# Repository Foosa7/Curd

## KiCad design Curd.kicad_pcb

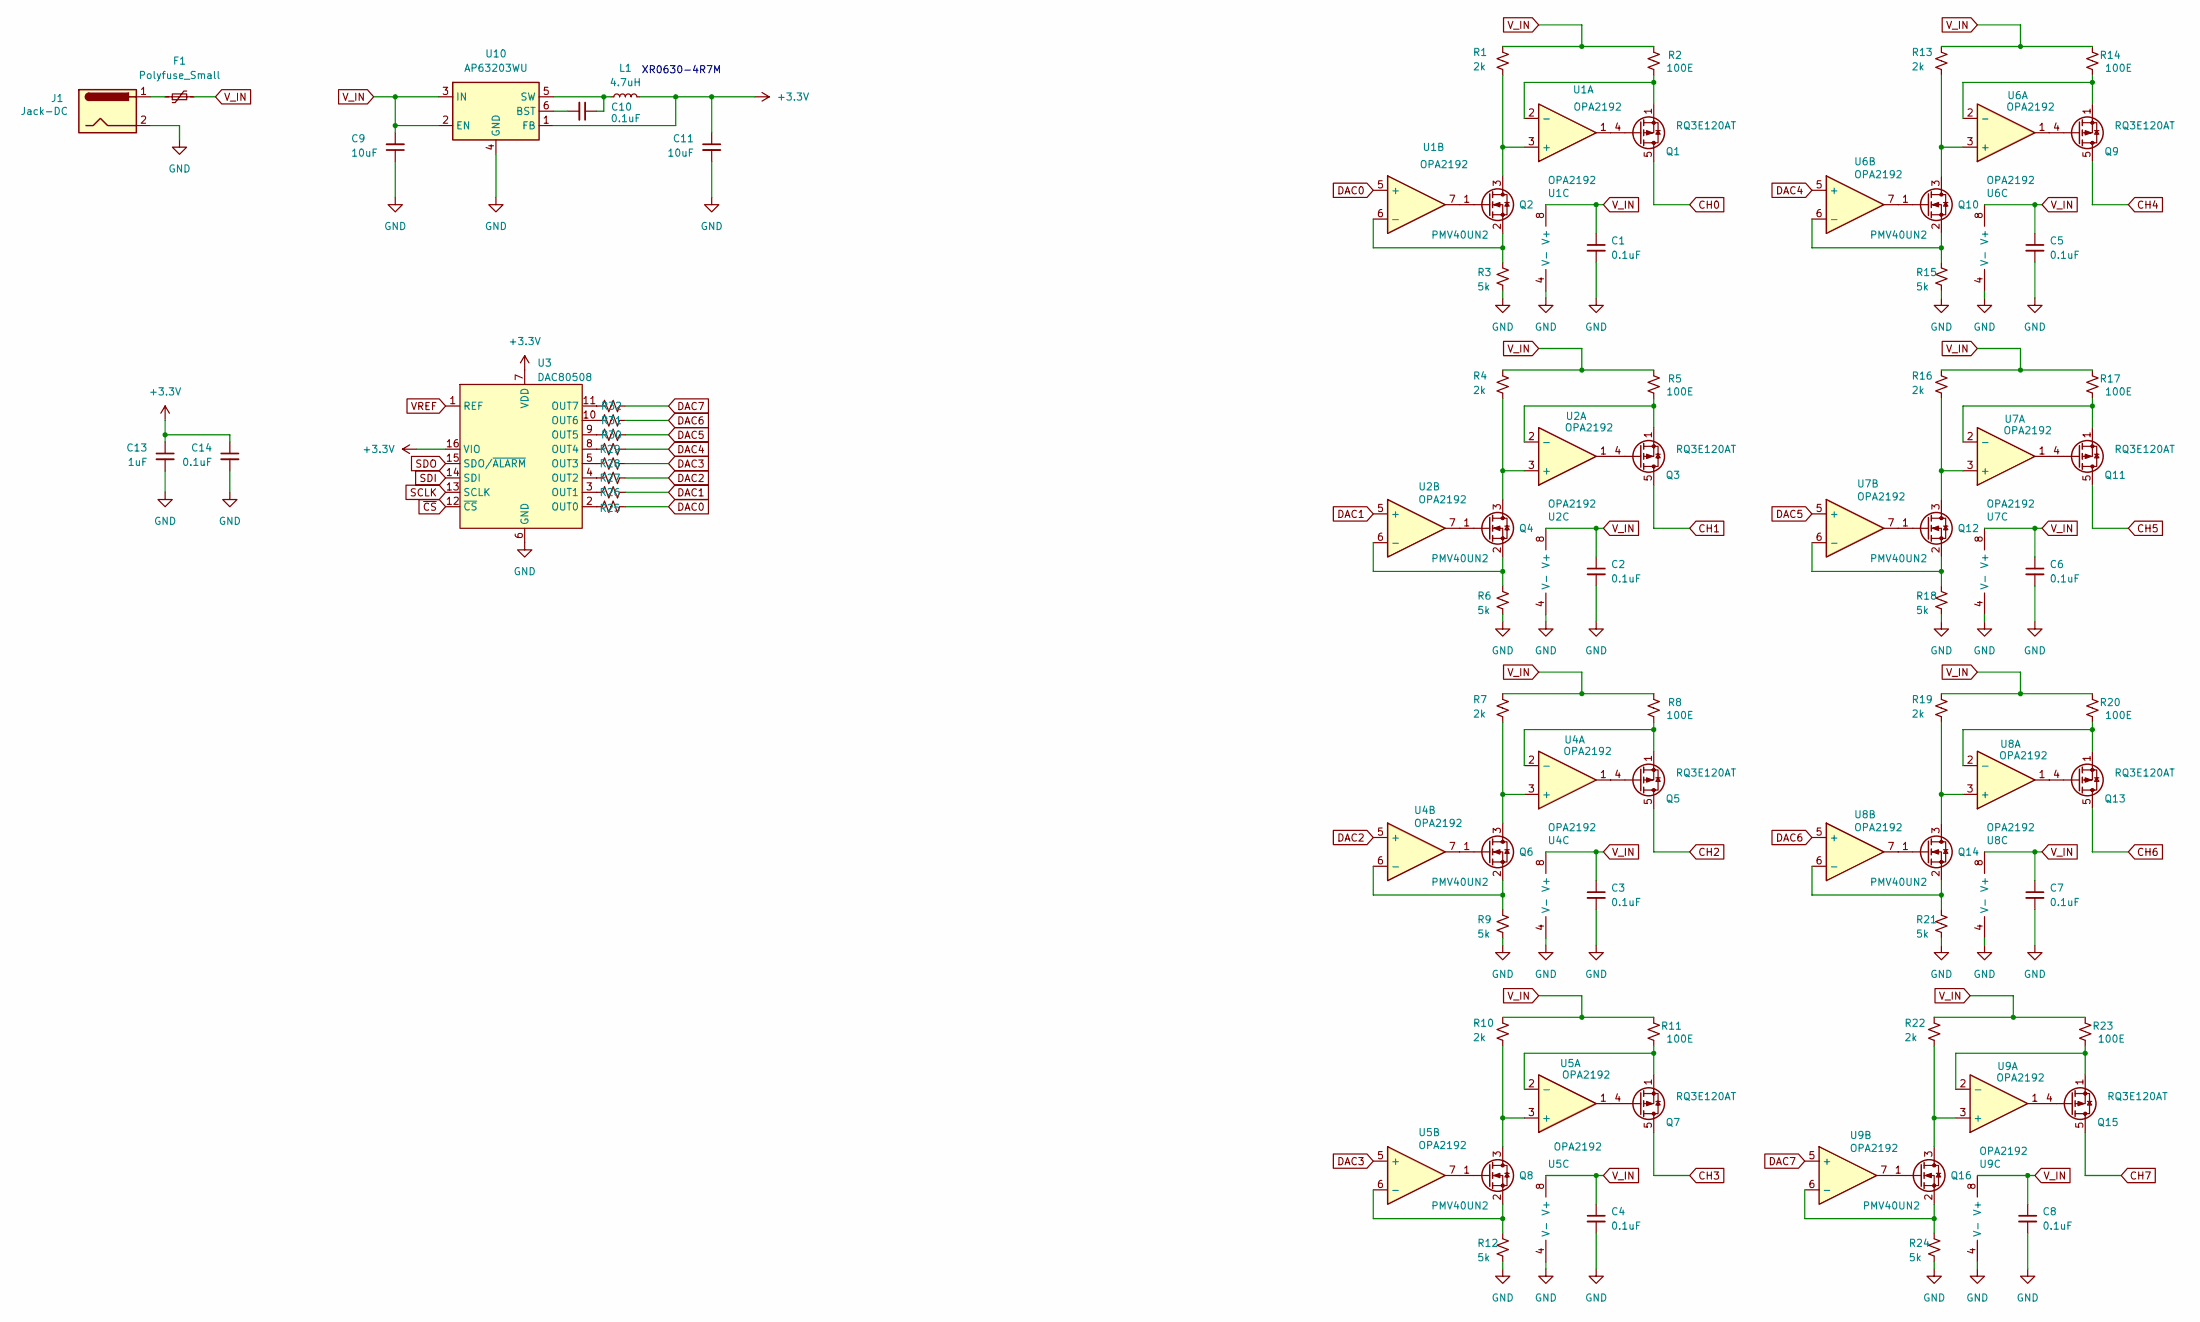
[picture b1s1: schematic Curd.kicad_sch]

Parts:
C1, C2, C3, C4, C5, C6, C7, C8, C10, C14: 0.1uF; C_0603_1608Metric
C9, C11: 10uF; C_0603_1608Metric
C13: 1uF; C_0603_1608Metric
F1: Polyfuse_Small
J1: Jack-DC
L1: 4.7uH; XR0630-4R7M
Q1, Q3, Q5, Q7, Q9, Q11, Q13, Q15: RQ3E120AT; HSMT8
Q2, Q4, Q6, Q8, Q10, Q12, Q14, Q16: PMV40UN2; SOT-23-3
R1, R4, R7, R10, R13, R16, R19, R22: 2k; R_0603_1608Metric
R2, R5, R8, R11, R14, R17, R20, R23: 100E; R_0603_1608Metric
R3, R6, R9, R12, R15, R18, R21, R24: 5k; R_0603_1608Metric
R25, R26, R27, R28, R29, R30, R31, R32: R_0603_1608Metric
U1, U2, U4, U5, U6, U7, U8, U9: OPA2192; SOIC-8_3.9x4.9mm_P1.27mm
U3: DAC80508; WQFN-16-1EP_3x3mm_P0.5mm_EP1.6x1.6mm
U10: AP63203WU; TSOT-23-6

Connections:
+3.3V: C11.1, C13.1, C14.1, L1.2, U3.7 (VDD), U3.16 (VIO), U10.1 (FB)
CH0: Q1.5, Q1.6 (D), Q1.7 (D), Q1.8 (D)
CH1: Q3.5, Q3.6 (D), Q3.7 (D), Q3.8 (D)
CH2: Q5.5, Q5.6 (D), Q5.7 (D), Q5.8 (D)
CH3: Q7.5, Q7.6 (D), Q7.7 (D), Q7.8 (D)
CH4: Q9.5, Q9.6 (D), Q9.7 (D), Q9.8 (D)
CH5: Q11.5, Q11.6 (D), Q11.7 (D), Q11.8 (D)
CH6: Q13.5, Q13.6 (D), Q13.7 (D), Q13.8 (D)
CH7: Q15.5, Q15.6 (D), Q15.7 (D), Q15.8 (D)
DAC0: R25.2, U1.5 (+)
DAC1: R26.2, U2.5 (+)
DAC2: R27.2, U4.5 (+)
DAC3: R28.2, U5.5 (+)
DAC4: R29.2, U6.5 (+)
DAC5: R30.2, U7.5 (+)
DAC6: R31.2, U8.5 (+)
DAC7: R32.2, U9.5 (+)
GND: C1.2, C2.2, C3.2, C4.2, C5.2, C6.2, C7.2, C8.2, C9.1, C11.2, C13.2, C14.2, J1.2, R3.2, R6.2, R9.2, R12.2, R15.2, R18.2, R21.2, R24.2, U1.4 (V-), U2.4 (V-), U3.6 (GND), U3.17 (THERMAL), U4.4 (V-), U5.4 (V-), U6.4 (V-), U7.4 (V-), U8.4 (V-), U9.4 (V-), U10.4 (GND)
unnamed: F1.1, J1.1
unnamed: Q1.4, U1.1
unnamed: Q2.1, U1.7
unnamed: Q3.4, U2.1
unnamed: Q4.1, U2.7
unnamed: Q5.4, U4.1
unnamed: Q6.1, U4.7
unnamed: Q7.4, U5.1
unnamed: Q8.1, U5.7
unnamed: Q9.4, U6.1
unnamed: Q10.1, U6.7
unnamed: Q11.4, U7.1
unnamed: Q12.1, U7.7
unnamed: Q13.4, U8.1
unnamed: Q14.1, U8.7
unnamed: Q15.4, U9.1
unnamed: Q16.1, U9.7
unnamed: Q2.3, R1.2, U1.3 (+)
unnamed: Q1.1, Q1.2 (S), Q1.3 (S), R2.1, U1.2 (-)
unnamed: Q2.2, R3.1, U1.6 (-)
unnamed: Q4.3, R4.2, U2.3 (+)
unnamed: Q3.1, Q3.2 (S), Q3.3 (S), R5.1, U2.2 (-)
unnamed: Q4.2, R6.1, U2.6 (-)
unnamed: R25.1, U3.2 (OUT0)
unnamed: R26.1, U3.3 (OUT1)
unnamed: R27.1, U3.4 (OUT2)
unnamed: R28.1, U3.5 (OUT3)
unnamed: R29.1, U3.8 (OUT4)
unnamed: R30.1, U3.9 (OUT5)
unnamed: R31.1, U3.10 (OUT6)
unnamed: R32.1, U3.11 (OUT7)
unnamed: Q6.3, R7.2, U4.3 (+)
unnamed: Q5.1, Q5.2 (S), Q5.3 (S), R8.1, U4.2 (-)
unnamed: Q6.2, R9.1, U4.6 (-)
unnamed: Q8.3, R10.2, U5.3 (+)
unnamed: Q7.1, Q7.2 (S), Q7.3 (S), R11.1, U5.2 (-)
unnamed: Q8.2, R12.1, U5.6 (-)
unnamed: Q10.3, R13.2, U6.3 (+)
unnamed: Q9.1, Q9.2 (S), Q9.3 (S), R14.1, U6.2 (-)
unnamed: Q10.2, R15.1, U6.6 (-)
unnamed: Q12.3, R16.2, U7.3 (+)
unnamed: Q11.1, Q11.2 (S), Q11.3 (S), R17.1, U7.2 (-)
unnamed: Q12.2, R18.1, U7.6 (-)
unnamed: Q14.3, R19.2, U8.3 (+)
unnamed: Q13.1, Q13.2 (S), Q13.3 (S), R20.1, U8.2 (-)
unnamed: Q14.2, R21.1, U8.6 (-)
unnamed: Q16.3, R22.2, U9.3 (+)
unnamed: Q15.1, Q15.2 (S), Q15.3 (S), R23.1, U9.2 (-)
unnamed: Q16.2, R24.1, U9.6 (-)
unnamed: C10.2, U10.6 (BST)
unnamed: C10.1, L1.1, U10.5 (SW)
SCLK: U3.13 (SCLK)
SDI: U3.14 (SDI)
SDO: U3.15 (SDO/~ALARM)
VREF: U3.1 (REF)
V_IN: C1.1, C2.1, C3.1, C4.1, C5.1, C6.1, C7.1, C8.1, C9.2, F1.2, R1.1, R2.2, R4.1, R5.2, R7.1, R8.2, R10.1, R11.2, R13.1, R14.2, R16.1, R17.2, R19.1, R20.2, R22.1, R23.2, U1.8 (V+), U2.8 (V+), U4.8 (V+), U5.8 (V+), U6.8 (V+), U7.8 (V+), U8.8 (V+), U9.8 (V+), U10.2 (EN), U10.3 (IN)
~CS: U3.12 (~CS)

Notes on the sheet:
XR0630-4R7M

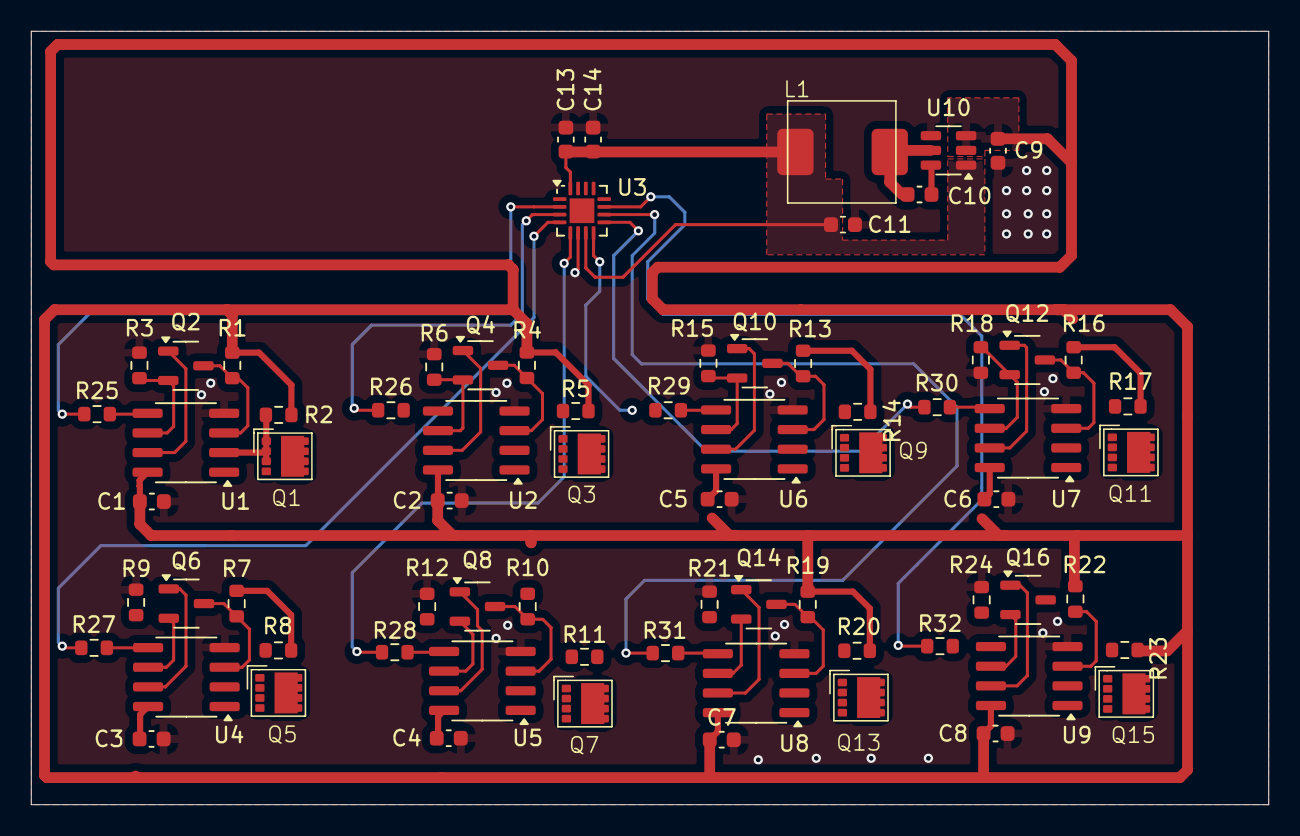
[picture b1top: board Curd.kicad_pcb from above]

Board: 4 copper layers, 80.0 x 50.0 mm, 72 parts (0 on the bottom side), 69 nets.

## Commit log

2025-03-19 Curd PCB
2025-03-19 KiCad git plugin
2025-03-20 Added routing
2025-03-20 Updated routing
